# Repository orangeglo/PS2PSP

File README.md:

# PS2PSP

These are PCB design and arduino software files for a circuit board that converts a PS2 controller into signals a PSP2000 motherboard can understand. The circuit board is designed to have the PSP power cable routed through it, so you can boot up the PSP and the adapter with a basic toggle switch.

[Order from OSH Park](https://oshpark.com/shared_projects/nhHJAzdG)

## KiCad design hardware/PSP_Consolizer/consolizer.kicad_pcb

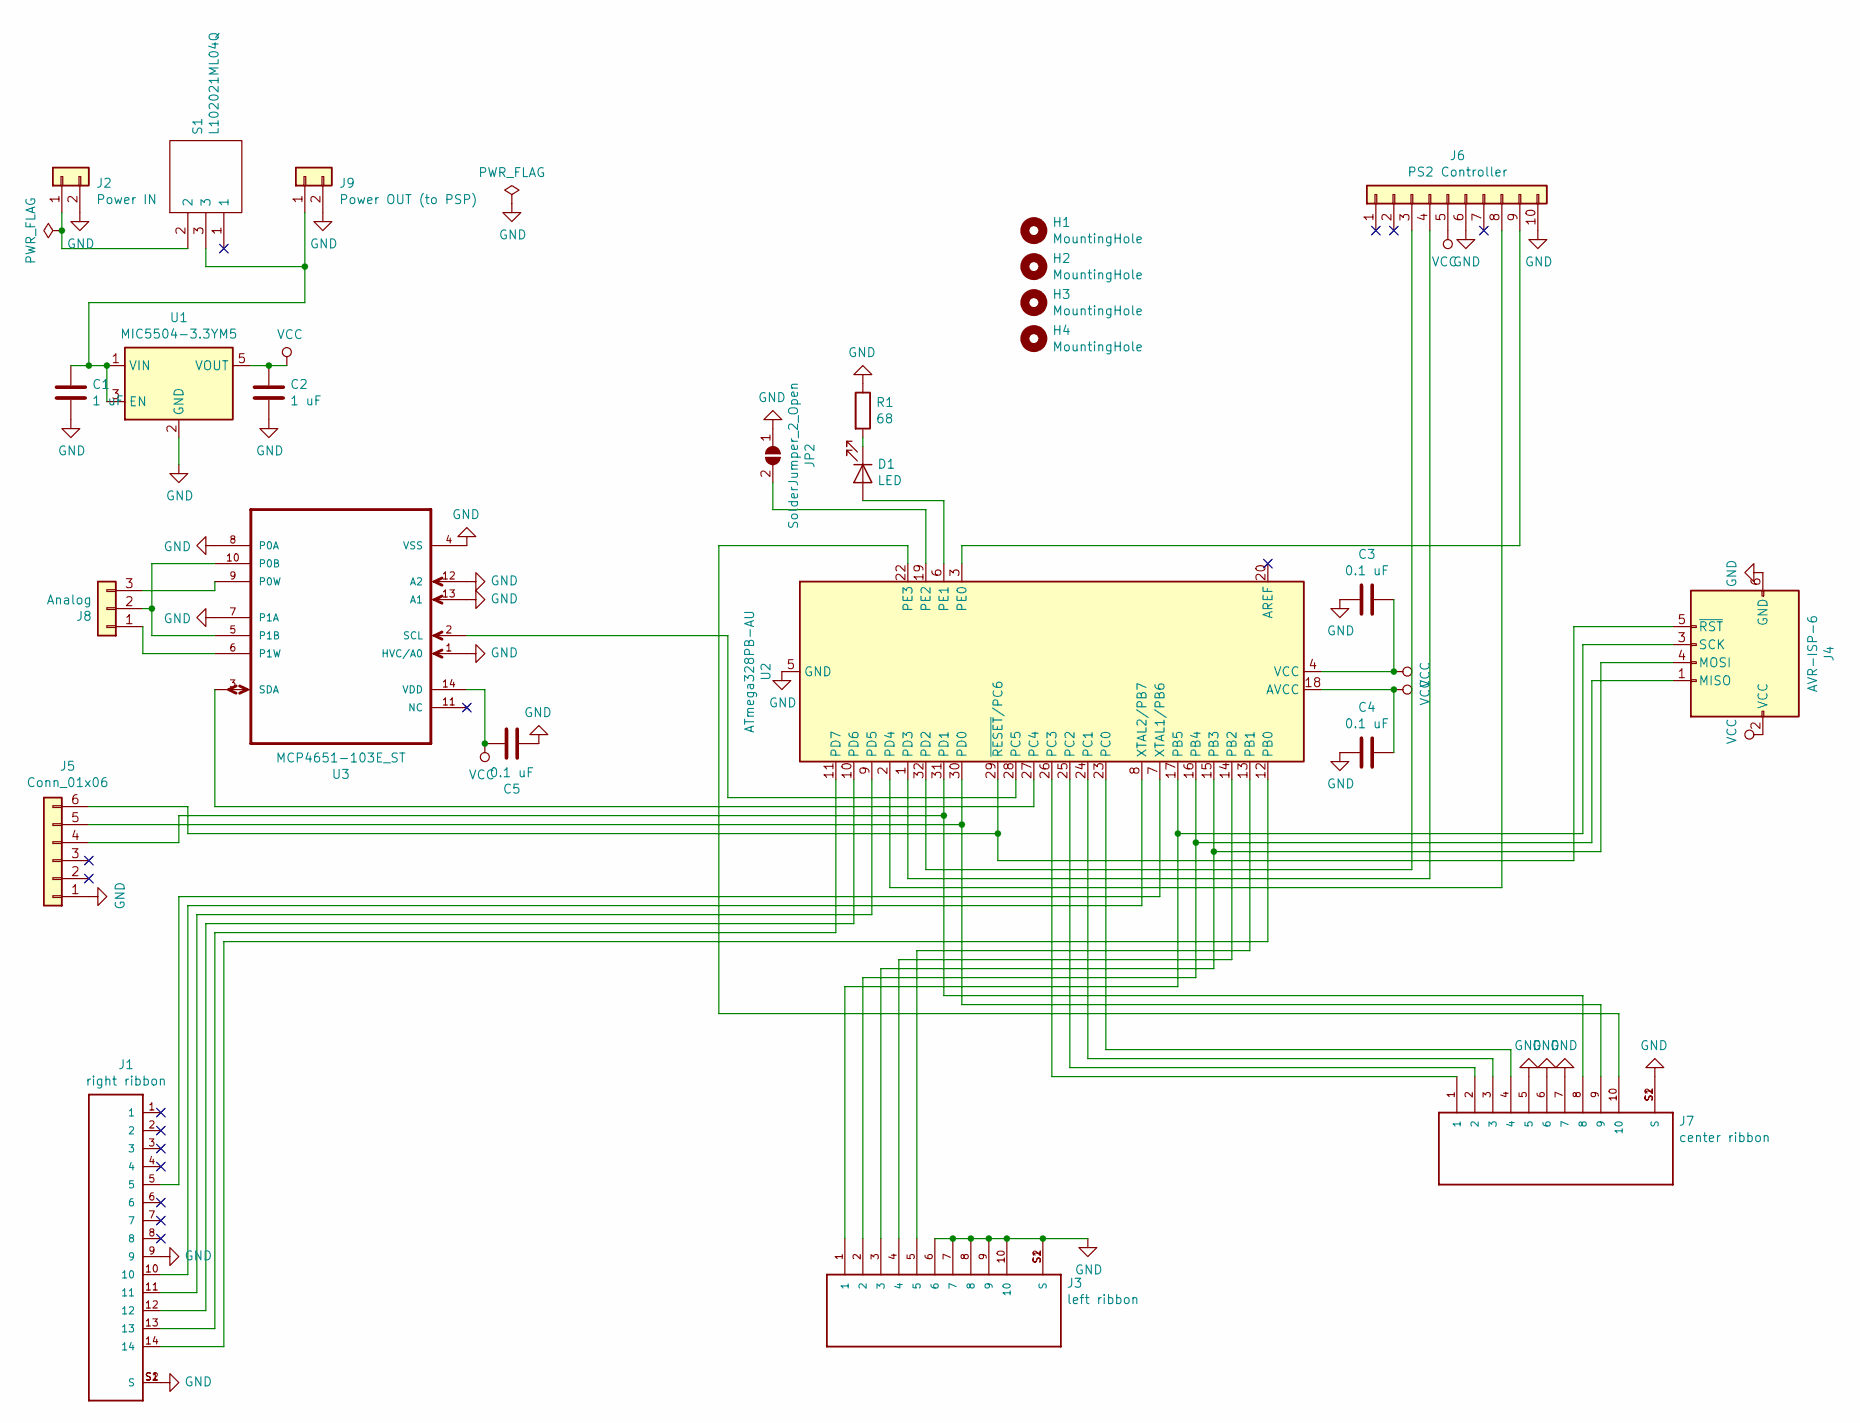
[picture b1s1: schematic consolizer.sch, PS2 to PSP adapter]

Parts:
C1, C2: 1 uF; C_0603_1608Metric_Pad1.05x0.95mm_HandSolder
C3, C4, C5: 0.1 uF; C_0603_1608Metric_Pad1.05x0.95mm_HandSolder
D1: LED; LED_0603_1608Metric_Pad1.05x0.95mm_HandSolder
H1, H2, H3, H4: MountingHole; MountingHole_2.2mm_M2
J1: right ribbon; TE_1-1734592-4
J2: Power IN; PinHeader_1x02_P2.54mm_Vertical
J3: left ribbon; TE_1-1734592-0
J4: AVR-ISP-6; PinHeader_2x03_P2.54mm_Vertical
J5: Conn_01x06; PinHeader_1x06_P2.54mm_Horizontal
J6: PS2 Controller; ps2_connector
J7: center ribbon; TE_1-1734592-0
J8: Analog; PinHeader_1x03_P2.54mm_Vertical
J9: Power OUT (to PSP); PinHeader_1x02_P2.54mm_Horizontal
JP2: SolderJumper_2_Open; SolderJumper-2_P1.3mm_Open_RoundedPad1.0x1.5mm
R1: 68; R_0603_1608Metric_Pad1.05x0.95mm_HandSolder
S1: L102021ML04Q; L102011ML04Q; Manufacturer_Part_Number L102021ML04Q; Mouser Part Number 611-L102021ML04Q
U1: MIC5504-3.3YM5; SOT-23-5
U2: ATmega328PB-AU; TQFP-32_7x7mm_P0.8mm
U3: MCP4651-103E_ST; SOP65P640X120-14N

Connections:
GND: C1.2, C2.2, C3.1, C4.1, C5.2, J1.9, J1.S1 (S), J1.S2 (S), J2.2, J3.6, J3.7, J3.8, J3.9, J3.10, J3.S1 (S), J3.S2 (S), J4.6 (GND), J5.1, J6.6, J6.10, J7.5, J7.6, J7.7, J7.S1 (S), J7.S2 (S), J9.2, JP2.1 (A), R1.1, U1.2 (GND), U2.5 (GND), U2.21 (GND), U3.1 (HVC/A0), U3.4 (VSS), U3.7 (P1A), U3.8 (P0A), U3.12 (A2), U3.13 (A1)
unnamed: C1.1, J9.1, S1.3, U1.1 (VIN), U1.3 (EN)
unnamed: D1.1 (K), R1.2
unnamed: D1.2 (A), U2.6 (PE1)
unnamed: J1.5, U2.7 (XTAL1/PB6)
unnamed: J1.10, U2.8 (XTAL2/PB7)
unnamed: J1.11, U2.9 (PD5)
unnamed: J1.12, U2.10 (PD6)
unnamed: J1.13, U2.11 (PD7)
unnamed: J1.14, U2.12 (PB0)
unnamed: J2.1, S1.2
unnamed: J3.1, J4.3 (SCK), U2.17 (PB5)
unnamed: J3.2, J4.1 (MISO), U2.16 (PB4)
unnamed: J3.3, J4.4 (MOSI), U2.15 (PB3)
unnamed: J3.4, U2.14 (PB2)
unnamed: J3.5, U2.13 (PB1)
unnamed: J4.5 (~RST), J5.6, U2.29 (~RESET~/PC6)
unnamed: J5.4, J7.8, U2.31 (PD1)
unnamed: J5.5, J7.9, U2.30 (PD0)
unnamed: J6.3, U2.32 (PD2)
unnamed: J6.4, U2.1 (PD3)
unnamed: J6.8, U2.2 (PD4)
unnamed: J6.9, U2.3 (PE0)
unnamed: J7.1, U2.26 (PC3)
unnamed: J7.2, U2.25 (PC2)
unnamed: J7.3, U2.24 (PC1)
unnamed: J7.4, U2.23 (PC0)
unnamed: J7.10, U2.22 (PE3)
unnamed: J8.1, U3.6 (P1W)
unnamed: J8.2, U3.5 (P1B), U3.10 (P0B)
unnamed: J8.3, U3.9 (P0W)
unnamed: JP2.2 (B), U2.19 (PE2)
unnamed: U2.27 (PC4), U3.3 (SDA)
unnamed: U2.28 (PC5), U3.2 (SCL)
VCC: C2.1, C3.2, C4.2, C5.1, J4.2 (VCC), J6.5, U1.5 (VOUT), U2.4 (VCC), U2.18 (AVCC), U3.14 (VDD)

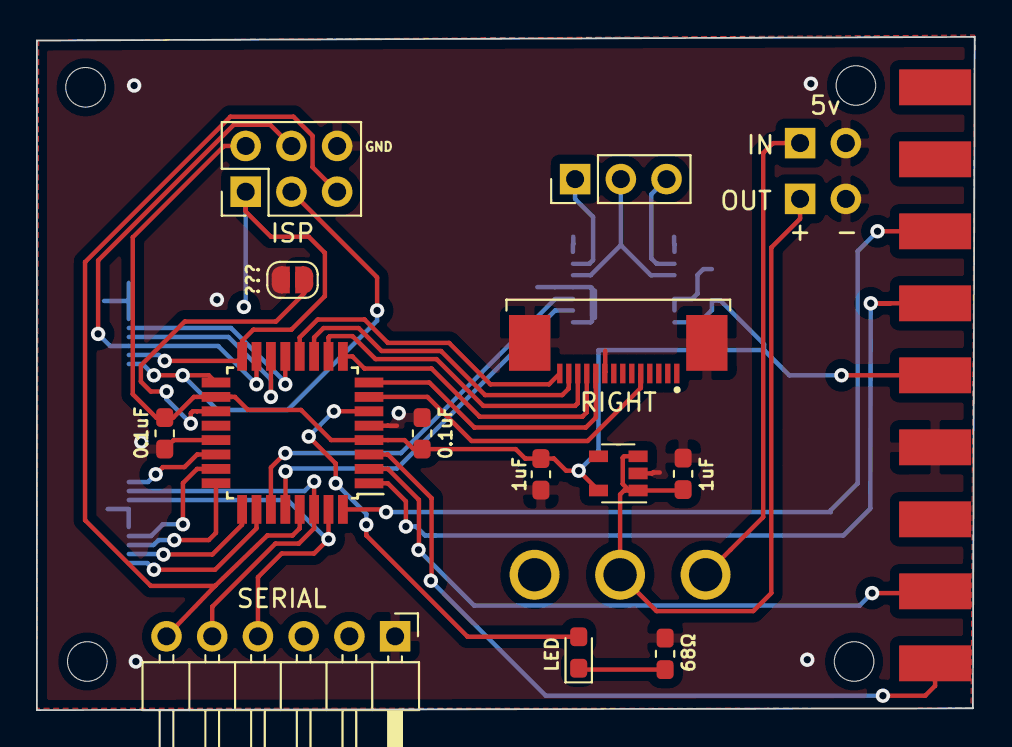
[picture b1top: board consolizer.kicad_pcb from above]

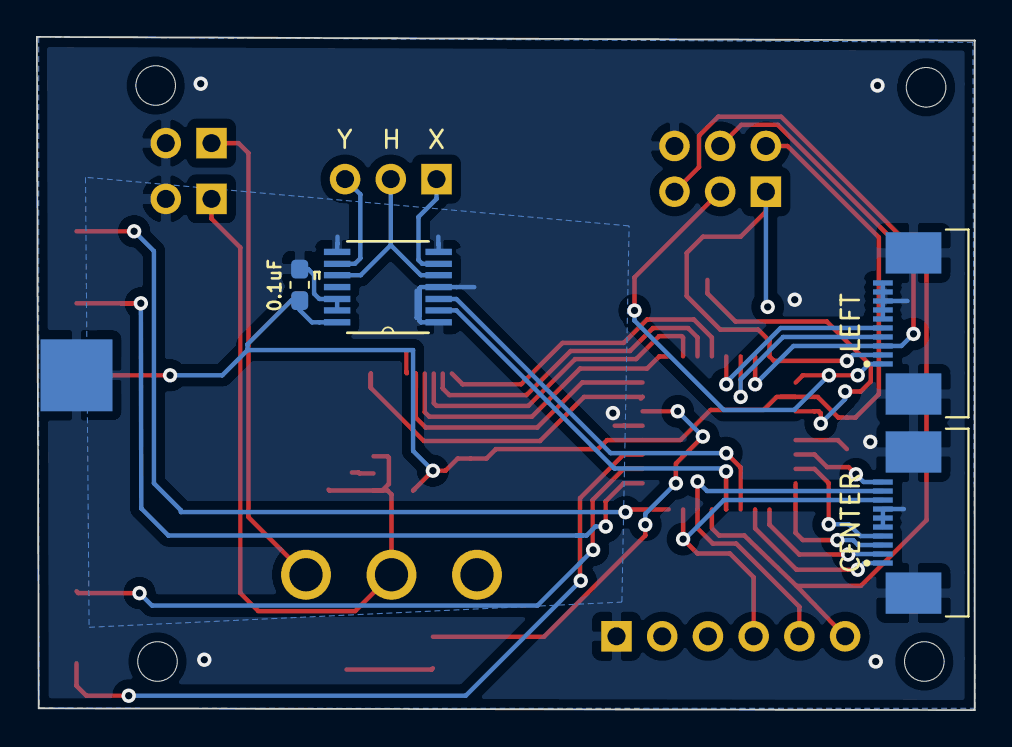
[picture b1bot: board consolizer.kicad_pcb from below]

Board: 2 copper layers, 52.1 x 37.4 mm, 25 parts (4 on the bottom side), 35 nets.

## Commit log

2020-01-17 add firmware
2020-01-17 Add secondary mode switching
2020-01-19 right stick working and other tweaks
2020-01-19 Cleanup and organize
2020-01-20 Add basic PWM mode for right analog
2020-03-14 Update firmware
2020-06-18 Update firmware and add kicad files
